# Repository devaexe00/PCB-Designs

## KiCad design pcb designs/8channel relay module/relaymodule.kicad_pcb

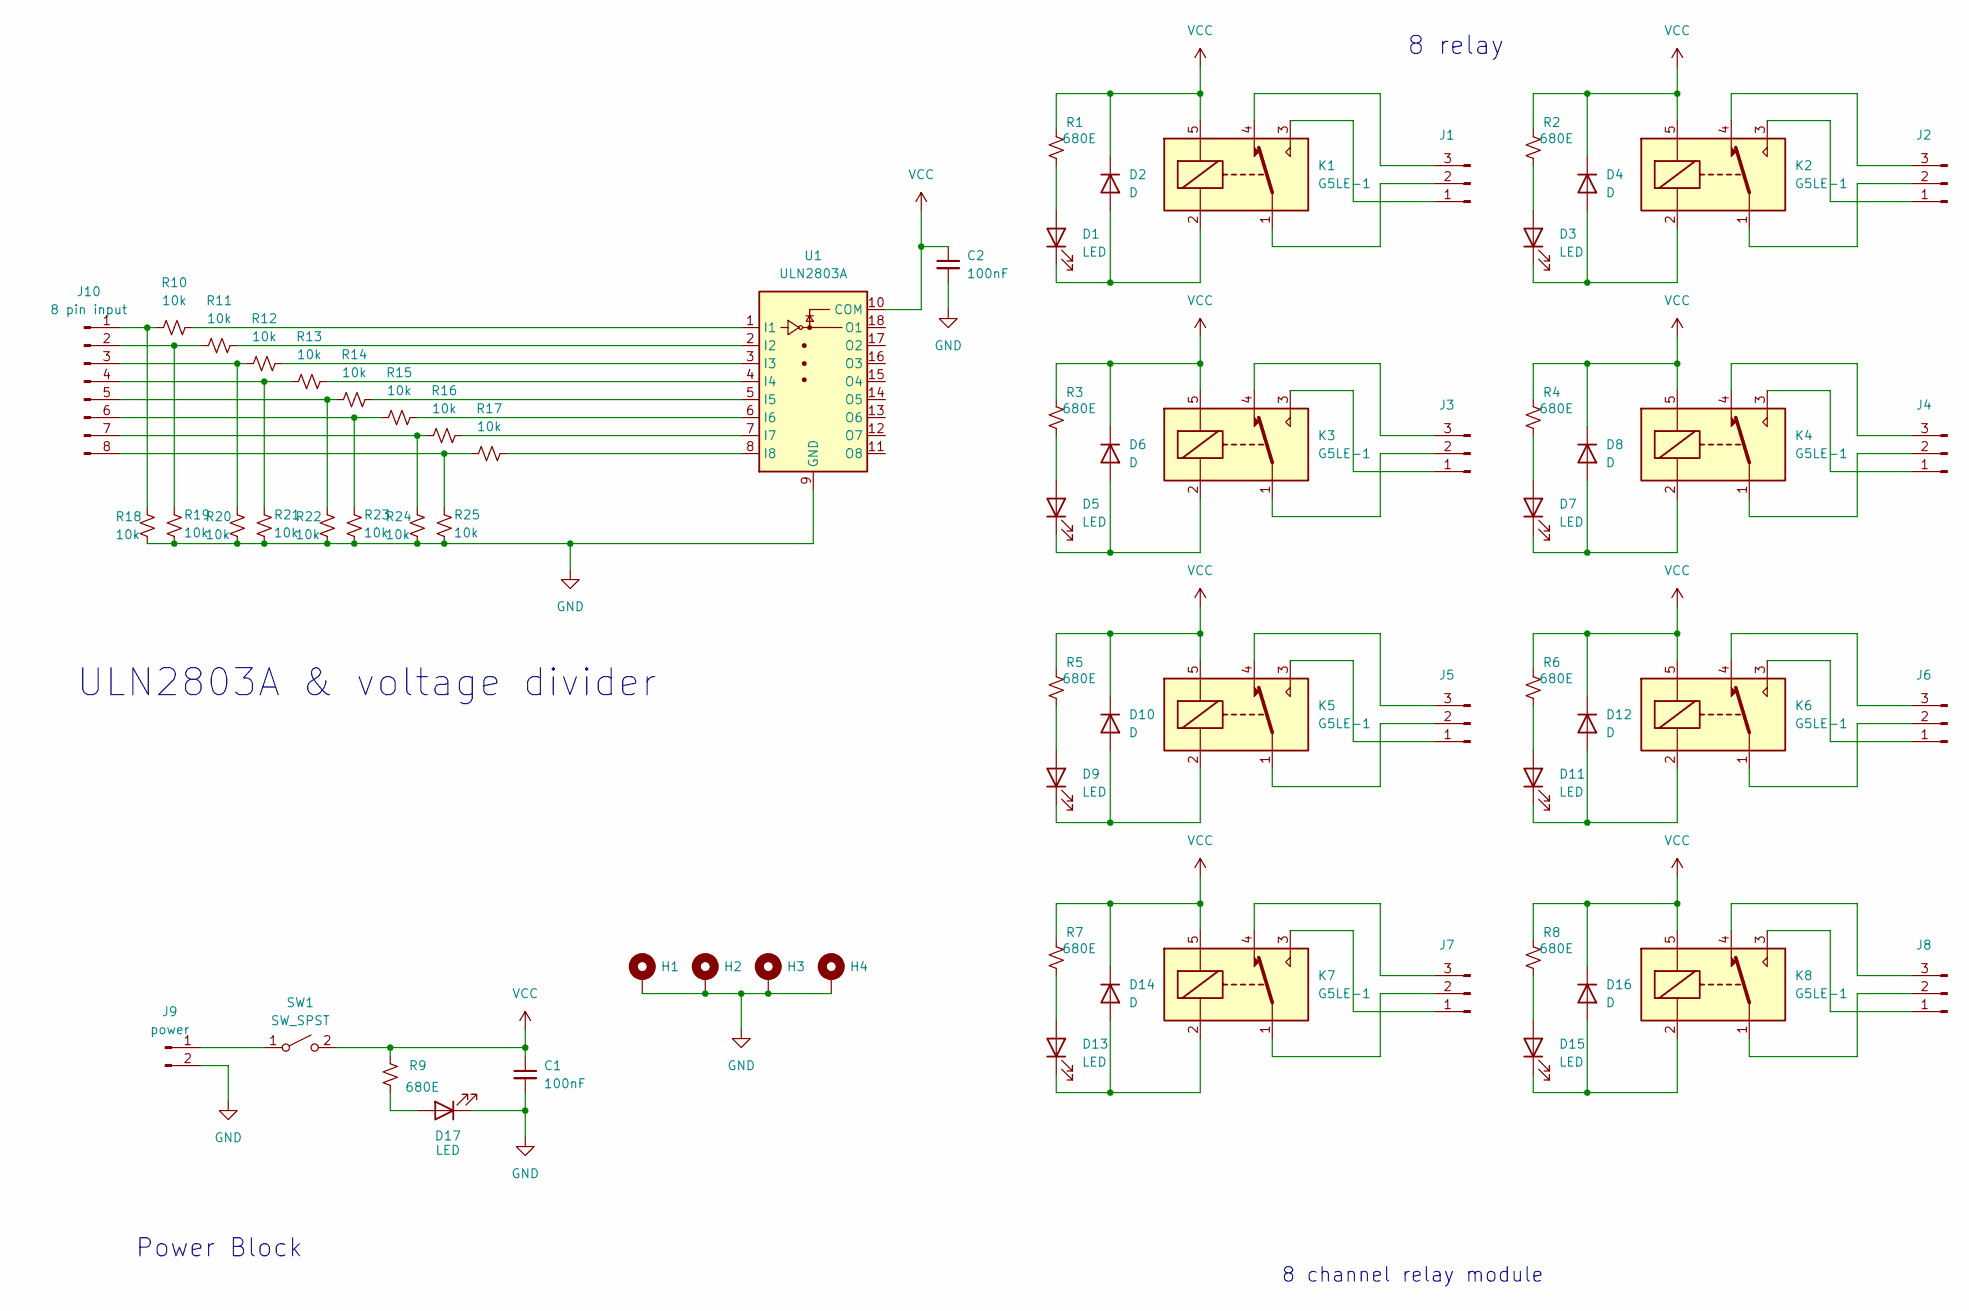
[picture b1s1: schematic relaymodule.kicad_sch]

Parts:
C1, C2: 100nF; C_0805_2012Metric_Pad1.18x1.45mm_HandSolder
D1, D3, D5, D7, D9, D11, D13, D15, D17: LED; LED_1206_3216Metric
D2, D4, D6, D8, D10, D12, D14, D16: D; D_1206_3216Metric
H1, H2, H3, H4: MountingHole_2.5mm_Pad_Via
J1, J2, J3, J4, J5, J6, J7, J8: JST_NV_B03P-NV_1x03_P5.00mm_Vertical
J9: power; JST_NV_B02P-NV_1x02_P5.00mm_Vertical
J10: 8 pin input; PinHeader_1x08_P2.54mm_Vertical
K1, K2, K3, K4, K5, K6, K7, K8: G5LE-1; Relay_SPDT_Omron-G5LE-1
R1, R2, R3, R4, R5, R6, R7, R8, R9: 680E; R_0805_2012Metric_Pad1.20x1.40mm_HandSolder
R10, R11, R12, R13, R14, R15, R16, R17, R18, R19, R20, R21, R22, R23, R24, R25: 10k; R_0805_2012Metric_Pad1.20x1.40mm_HandSolder
SW1: SW_SPST; Panasonic_EVQPUJ_EVQPUA
U1: ULN2803A; DIP-18_W7.62mm

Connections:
GND: C1.2, C2.2, D17.1 (K), H1.1, H2.1, H3.1, H4.1, J9.2, R18.2, R19.2, R20.2, R21.2, R22.2, R23.2, R24.2, R25.2, U1.9 (GND)
unnamed: D1.2 (A), R1.2
unnamed: D1.1 (K), D2.2 (A), K1.2
unnamed: D3.2 (A), R2.2
unnamed: D3.1 (K), D4.2 (A), K2.2
unnamed: D5.2 (A), R3.2
unnamed: D5.1 (K), D6.2 (A), K3.2
unnamed: D7.2 (A), R4.2
unnamed: D7.1 (K), D8.2 (A), K4.2
unnamed: D9.2 (A), R5.2
unnamed: D9.1 (K), D10.2 (A), K5.2
unnamed: D11.2 (A), R6.2
unnamed: D11.1 (K), D12.2 (A), K6.2
unnamed: D13.2 (A), R7.2
unnamed: D13.1 (K), D14.2 (A), K7.2
unnamed: D15.2 (A), R8.2
unnamed: D15.1 (K), D16.2 (A), K8.2
unnamed: D17.2 (A), R9.2
unnamed: J1.1, K1.3
unnamed: J1.2, K1.1
unnamed: J1.3, K1.4
unnamed: J2.1, K2.3
unnamed: J2.2, K2.1
unnamed: J2.3, K2.4
unnamed: J3.1, K3.3
unnamed: J3.2, K3.1
unnamed: J3.3, K3.4
unnamed: J4.1, K4.3
unnamed: J4.2, K4.1
unnamed: J4.3, K4.4
unnamed: J5.1, K5.3
unnamed: J5.2, K5.1
unnamed: J5.3, K5.4
unnamed: J6.1, K6.3
unnamed: J6.2, K6.1
unnamed: J6.3, K6.4
unnamed: J7.1, K7.3
unnamed: J7.2, K7.1
unnamed: J7.3, K7.4
unnamed: J8.1, K8.3
unnamed: J8.2, K8.1
unnamed: J8.3, K8.4
unnamed: J9.1, SW1.1 (A)
unnamed: J10.1, R10.1, R18.1
unnamed: J10.2, R11.1, R19.1
unnamed: J10.3, R12.1, R20.1
unnamed: J10.4, R13.1, R21.1
unnamed: J10.5, R14.1, R22.1
unnamed: J10.6, R15.1, R23.1
unnamed: J10.7, R16.1, R24.1
unnamed: J10.8, R17.1, R25.1
unnamed: R10.2, U1.1 (I1)
unnamed: R11.2, U1.2 (I2)
unnamed: R12.2, U1.3 (I3)
unnamed: R13.2, U1.4 (I4)
unnamed: R14.2, U1.5 (I5)
unnamed: R15.2, U1.6 (I6)
unnamed: R16.2, U1.7 (I7)
unnamed: R17.2, U1.8 (I8)
VCC: C1.1, C2.1, D2.1 (K), D4.1 (K), D6.1 (K), D8.1 (K), D10.1 (K), D12.1 (K), D14.1 (K), D16.1 (K), K1.5, K2.5, K3.5, K4.5, K5.5, K6.5, K7.5, K8.5, R1.1, R2.1, R3.1, R4.1, R5.1, R6.1, R7.1, R8.1, R9.1, SW1.2 (B), U1.10 (COM)

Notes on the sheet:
Power Block
8 channel relay module
8 relay
ULN2803A & voltage divider

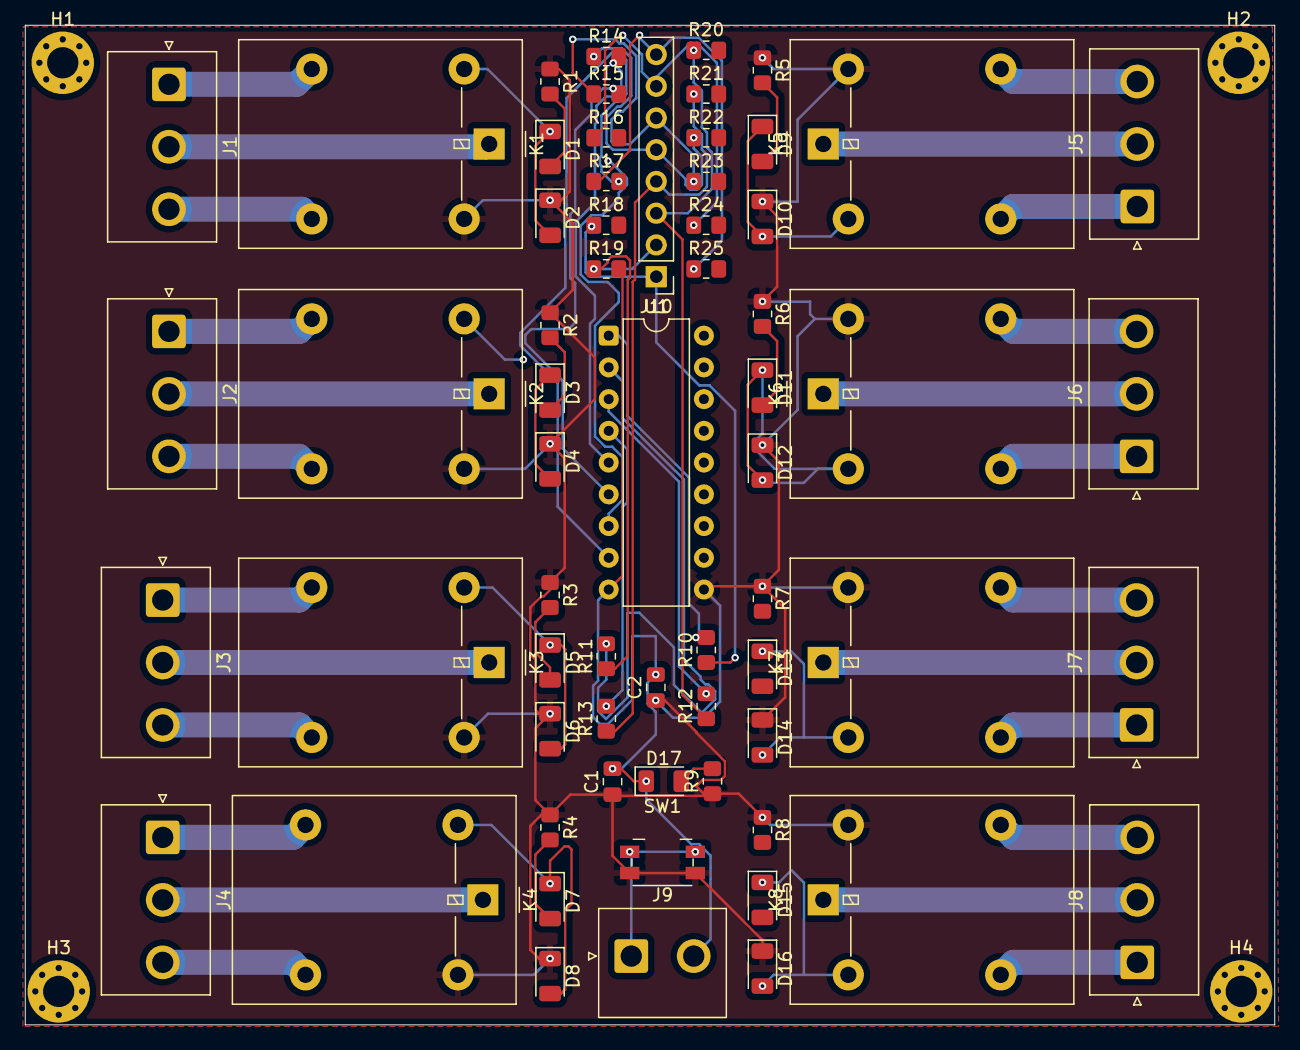
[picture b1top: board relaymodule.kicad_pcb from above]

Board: 2 copper layers, 100.0 x 80.0 mm, 68 parts (0 on the bottom side), 60 nets.
